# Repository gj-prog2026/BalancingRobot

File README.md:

# Balancing Robot

## Introduction
This is an ongoing personal project started on 02/08/2026. Up to 17/09/2026 the budget was kept within £60. The aim is to build a self-balancing robot and learn about control. PID tuning was unsuccessful, so I moved to LQR.

## Hardware
Both the PCB and the robot frame were designed by me, with the PCB manufactured by JLCPCB and the frame 3D printed at home. The bottom layer and motor brackets take the most vibration, so carbon-fibre PETG was chosen for its rigidity. The rest of the frame is PLA, which was easier to print and has no special strength requirement.

Main parts: STM32F103C8T6 (Blue Pill), TB6612FNG motor driver, GA12-N20 500 rpm geared motors with Hall encoders, a GY-521 IMU board (it carries an ICM-20689 rather than an MPU6050, but the firmware still calls it MPU6050), an HC-05 for Bluetooth, and 4×AA cells.

## Software
Development was staged so each part was verified before the next:

| Stage | Purpose | Status |
|---|---|---|
| 0 | Confirm the clock ticks are generated correctly | Done |
| 1 | Read gyroscope and accelerometer over I2C and fuse a pitch angle | Done |
| 2 | Send IMU data to the laptop over UART via HC-05 | Done |
| 3 | Receive commands over Bluetooth and check the motors respond | Done |
| 4 | PID balancing attempt | Did not balance |
| 5 | LQR controller with gains from the MATLAB model | Balances hands-off, best runs 20-40 s; runs vary, tuning continues |

See [software](software/) for the firmware, test logs and a note on how Claude was used.

## MATLAB simulation
After PID failed despite continued tuning, I hypothesised the 500 rpm motors didn't have enough torque. I simulated the robot in MATLAB and the results showed there is theoretically enough torque. Later system identification on the real robot agreed: the motors behave close to the model.

To reduce development time I then chose LQR, with the model tested and simulated in MATLAB. I measured the period of oscillation in a pendulum test to get the inertia, plus the height from the centre of mass to the wheel axis, the encoder CPR, the mass and the wheel radius. The MATLAB simulation files were generated by Claude, as I was new to MATLAB.

## What was really wrong
The LQR ported from the simulation failed within 1-2 s on hardware. I added logging (a RAM log dumped over Bluetooth after each run) and, with Claude's help analysing the logs, found that the angle and rate reached the controller about 20-30 ms later than the wheel encoder. The simulation had missed this because it delayed all signals together. A model of the firmware's exact signal path showed that this uneven lag makes the loop unstable. Raising the IMU sample rate to 1 kHz and widening the gyro filter took the robot from falling in 1-2 s to balancing for 20-40 s.

My earlier hypothesis that motor deadband was the root cause turned out to be only a secondary effect: the log shows the wheels don't move until the command reaches about 0.5-1 V, and I'm testing compensation for that.

## Current Result
The longest run is 40 s (ended when I tripped it), with the code in `software/known_good_firmware`. A demo clip is in [demo video](demo/first_success_clip.gif). Pitch is controlled, but position holding is not working yet: the robot surges forward and backward over 1-2 m, chatters at about 8 Hz with the motor command saturated about half the time, and falls when the wheels reach their no-load speed. This is what I'm working on now.

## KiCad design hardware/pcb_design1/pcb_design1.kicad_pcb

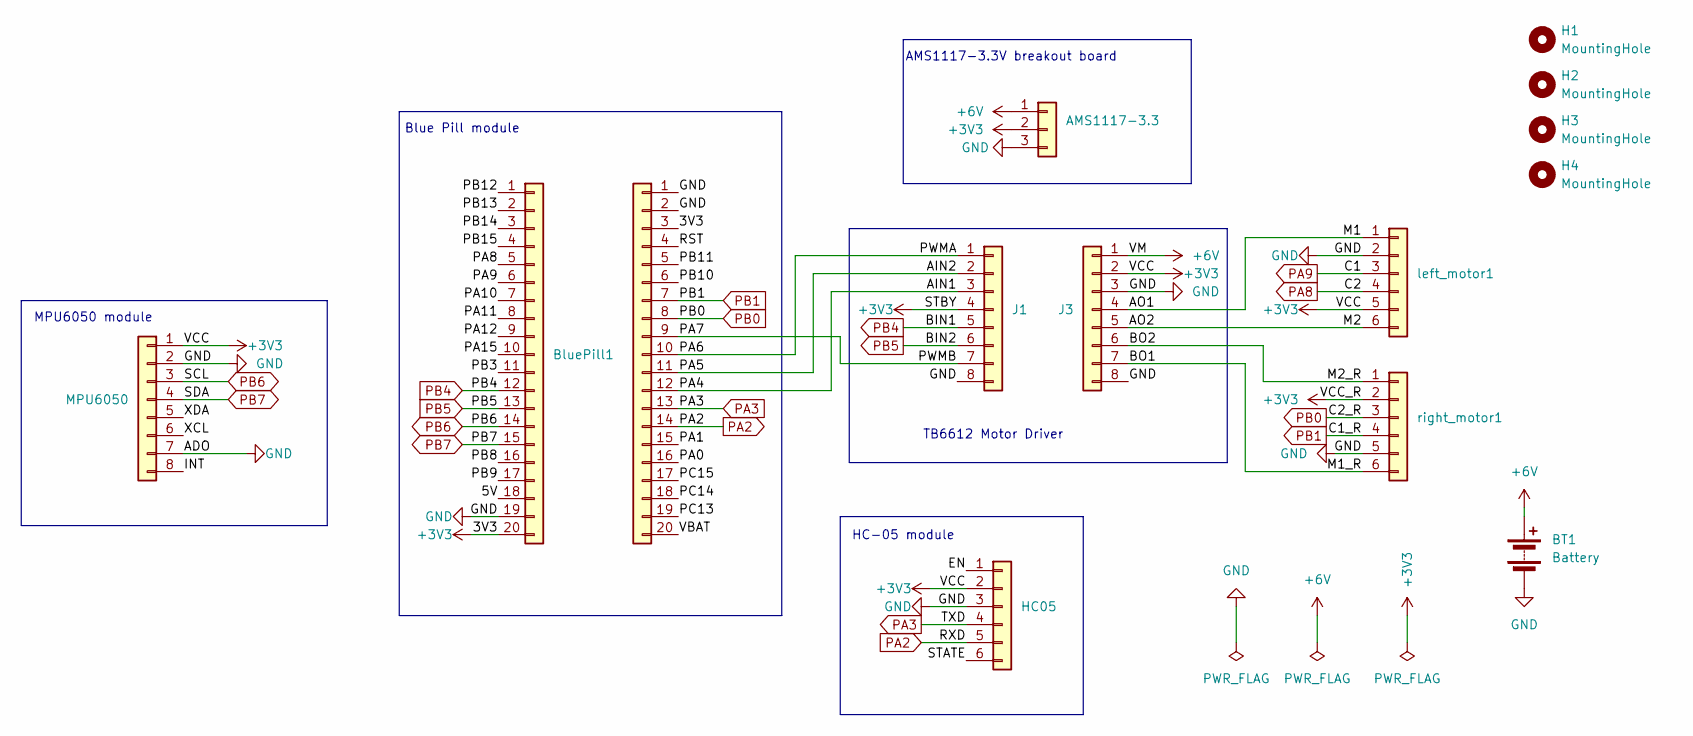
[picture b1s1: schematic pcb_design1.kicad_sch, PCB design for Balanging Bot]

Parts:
AMS1117-3.3: Conn_01x03; PinSocket_1x03_P2.54mm_Vertical
BT1: Battery; TerminalBlock_MaiXu_MX126-5.0-02P_1x02_P5.00mm
BluePill1: Conn_01x20; PinSocket_1x20_P2.54mm_Vertical
H1, H2, H3, H4: MountingHole; MountingHole_3.2mm_M3_ISO7380
HC05: Conn_01x06; PinSocket_1x06_P2.54mm_Vertical
J1, J3: Conn_01x08; PinSocket_1x08_P2.54mm_Vertical
J2: Conn_01x20; PinSocket_1x20_P2.54mm_Vertical
MPU6050: Conn_01x08; PinSocket_1x08_P2.54mm_Vertical
left_motor1: Conn_01x06; PinHeader_1x06_P2.54mm_Vertical
right_motor1: Conn_01x06; PinHeader_1x06_P2.54mm_Vertical

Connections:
+3V3: AMS1117-3.3.2, BluePill1.20, HC05.2, J1.4, J2.3, J3.2, MPU6050.1, left_motor1.5, right_motor1.2; also elsewhere on the board
+6V: AMS1117-3.3.1, BT1.1 (+), J3.1; also elsewhere on the board
/5V: BluePill1.18
/AIN1: J1.3, J2.12
/AIN2: J1.2, J2.11
/AO1: J3.4, left_motor1.1; also elsewhere on the board
/AO2: J3.5, left_motor1.6; also elsewhere on the board
/BO1: J3.7, right_motor1.6; also elsewhere on the board
/BO2: J3.6, right_motor1.1; also elsewhere on the board
/EN: HC05.1
/INT: MPU6050.8
/PA0: J2.16
/PA1: J2.15
/PA6: J1.1, J2.10
/PA7: J1.7, J2.9
/PA10: BluePill1.7
/PA11: BluePill1.8
/PA12: BluePill1.9
/PA15: BluePill1.10
/PB3: BluePill1.11
/PB8: BluePill1.16
/PB9: BluePill1.17
/PB10: J2.6
/PB11: J2.5
/PB12: BluePill1.1
/PB13: BluePill1.2
/PB14: BluePill1.3
/PB15: BluePill1.4
/PC13: J2.19
/PC14: J2.18
/PC15: J2.17
/RST: J2.4
/STATE: HC05.6
/VBAT: J2.20
/XCL: MPU6050.6
/XDA: MPU6050.5
GND: AMS1117-3.3.3, BT1.2 (-), BluePill1.19, HC05.3, J1.8, J2.1, J2.2, J3.3, J3.8, MPU6050.2, MPU6050.7, left_motor1.2, right_motor1.5; also elsewhere on the board
PA2: HC05.5, J2.14
PA3: HC05.4, J2.13
PA8: BluePill1.5, left_motor1.4
PA9: BluePill1.6, left_motor1.3
PB0: J2.8, right_motor1.3
PB1: J2.7, right_motor1.4
PB4: BluePill1.12, J1.5
PB5: BluePill1.13, J1.6
PB6: BluePill1.14, MPU6050.3
PB7: BluePill1.15, MPU6050.4

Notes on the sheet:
AMS1117-3.3V breakout board
MPU6050 module
TB6612 Motor Driver
HC-05 module
Blue Pill module

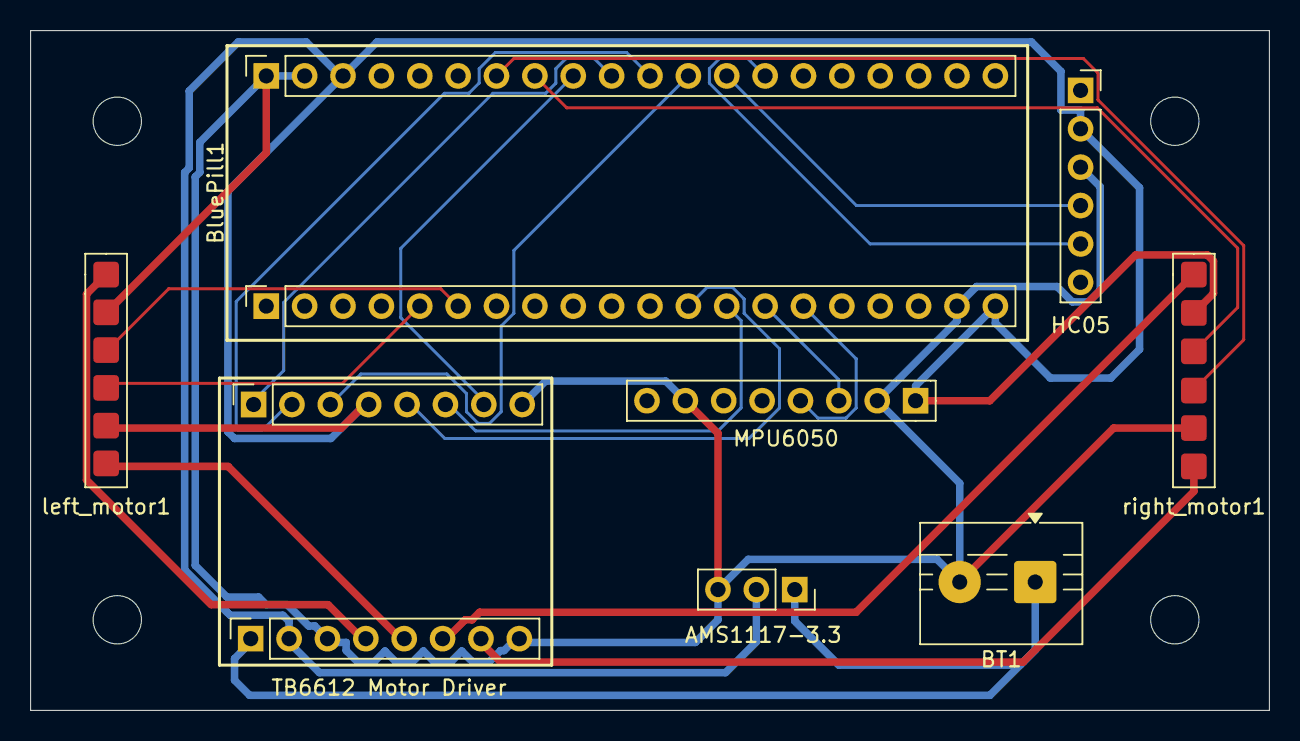
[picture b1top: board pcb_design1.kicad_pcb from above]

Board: 2 copper layers, 82.0 x 45.0 mm, 14 parts (0 on the bottom side), 21 nets.

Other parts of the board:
TB6612 Motor Driver: Conn_01x08; PinSocket_1x08_P2.54mm_Vertical

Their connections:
+3V3: TB6612 Motor Driver.2; also elsewhere on the board
+6V: TB6612 Motor Driver.1; also elsewhere on the board
/AO1: TB6612 Motor Driver.4; also elsewhere on the board
/AO2: TB6612 Motor Driver.5; also elsewhere on the board
/BO1: TB6612 Motor Driver.7; also elsewhere on the board
/BO2: TB6612 Motor Driver.6; also elsewhere on the board
GND: TB6612 Motor Driver.3, TB6612 Motor Driver.8; also elsewhere on the board
